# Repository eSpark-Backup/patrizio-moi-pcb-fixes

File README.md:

# PatrizioMoi-PCBFixes

Each product is a audio instrument, where the ESP32 receives audio signals from Ethernet ports (so the Ethernet port and ESP32 must communicate well), and each knob/button/toggle switch sends value signals to the ESP32 for audio processing. The way the audio will be processed it's not an issue right now, because it will be programmed by audio specialist. Your job is to design the 4 PCBS above in a way that

(i) each rotary switch, potentiometers, toggle switch, buttons, etc is aligned wiht the silkscreen and connected to the right pins;  
(ii) each rotary switch, potentiometers, toggle switch, buttons, etc sends signals to the ESP32 correctly;  
(iii) the entire PCB is well powered and fully functioning as desired.

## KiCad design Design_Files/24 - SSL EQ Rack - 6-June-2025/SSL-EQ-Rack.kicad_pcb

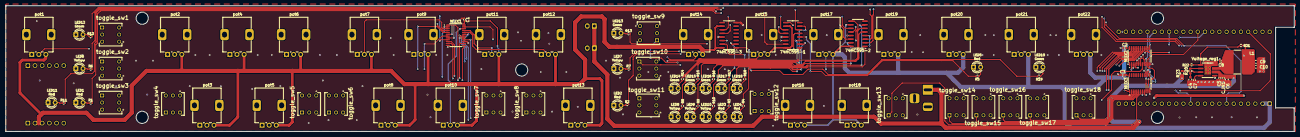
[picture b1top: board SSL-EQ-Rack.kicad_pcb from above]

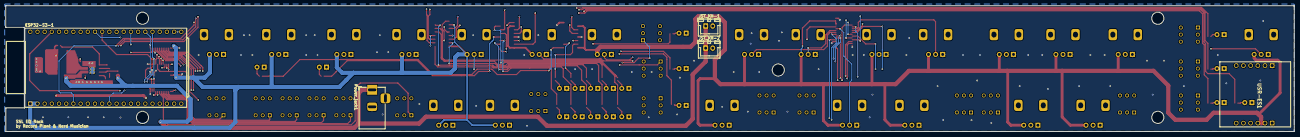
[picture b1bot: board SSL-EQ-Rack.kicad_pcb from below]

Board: 4 copper layers, 455.1 x 44.4 mm, 106 parts (5 on the bottom side), 106 nets.

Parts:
74HC595-1, 74HC595-2, 74HC595-3: 74HC595; SOIC-16_3.9x9.9mm_P1.27mm
C1, C2, C3: 0.1uF; C_0402_1005Metric
C4: 3.3 nF; C_0603_1608Metric
C5, C7, C8: 0.1 µF; C_0402_1005Metric
C6, C9, C10: 22uF; C_0603_1608Metric
C_IN1: 4.7 µF; C_0402_1005Metric
ESP32-S3-1: ESP32-S3-DevKitC; ESP32-S3-DEVKITC-1-N8R2-2
JST_XH-1, JST_XH-2: JST_XH_2_Pin; JST_XH_B2B-XH-A_1x02_P2.50mm_Vertical
L1: 10µH; L_Bourns-SRN8040_8x8.15mm
LED1, LED2, LED3, LED4, LED5, LED11: Red; LED_D3.0mm_Clear-2
LED6, LED7, LED8, LED9, LED10: Yellow; LED_D3.0mm_Clear-2
LED12, LED13, LED14, LED15, LED16, LED17, LED18, LED19: Green; LED_D3.0mm_Clear-2
MUX1, MUX2, MUX3: CD4067BMT/TR; TSSOP-24_4.4x7.8mm_P0.65mm
Power_jack1: Jack-DC; BarrelJack_Horizontal
R1, R2, R3, R4, R5, R6, R7, R8, R9, R10, R11, R12, R13, R14, R15, R16, R17, R18, R19: 330Ω; R_0402_1005Metric
R20: 6.8kΩ; R_0603_1608Metric
R21: 43 kΩ; R_0402_1005Metric
R22: 10 kΩ; R_0402_1005Metric
R23: 100kΩ; R_0603_1608Metric
USR-ES1: USR-ES1; USRES1
Voltage_reg1: MP2307DN-LF-Z; SOIC-8-1EP_3.9x4.9mm_P1.27mm_EP2.29x3mm_ThermalVias
pot1, pot2, pot3, pot4, pot5, pot6, pot7, pot8, pot9, pot10, pot11, pot12, pot13, pot14, pot15, pot16, pot17, pot18, pot19, pot20, pot21, pot22: b10k; Potentiometer_Alps_RK09K_Single_Vertical
toggle_sw1, toggle_sw2, toggle_sw3, toggle_sw4, toggle_sw5, toggle_sw6, toggle_sw7, toggle_sw8, toggle_sw9, toggle_sw10, toggle_sw11, toggle_sw12, toggle_sw13, toggle_sw14, toggle_sw15, toggle_sw16, toggle_sw17, toggle_sw18: button; SW_TL2285EE

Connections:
3.3V: 74HC595-1.10 (~SRCLR), 74HC595-1.16 (VCC), 74HC595-2.10 (~SRCLR), 74HC595-2.16 (VCC), 74HC595-3.10 (~SRCLR), 74HC595-3.16 (VCC), C1.2, C2.2, C3.2, ESP32-S3-1.1 (3V3), ESP32-S3-1.2 (3V3), MUX1.24 (VCC), MUX2.24 (VCC), MUX3.24 (VCC), USR-ES1.B2 (3V3_1), USR-ES1.B3 (3V3_2), pot1.3, pot2.3, pot3.3, pot4.3, pot5.3, pot6.3, pot7.3, pot8.3, pot9.3, pot10.3, pot11.3, pot12.3, pot13.3, pot14.3, pot15.3, pot16.3, pot17.3, pot18.3, pot19.3, pot20.3, pot21.3, pot22.3
/LEDs/LED_A_QA: 74HC595-1.15 (QA), R1.2
/LEDs/LED_A_QB: 74HC595-1.1 (QB), R2.2
/LEDs/LED_A_QC: 74HC595-1.2 (QC), R3.2
/LEDs/LED_A_QD: 74HC595-1.3 (QD), R4.2
/LEDs/LED_A_QE: 74HC595-1.4 (QE), R5.2
/LEDs/LED_A_QF: 74HC595-1.5 (QF), R7.2
/LEDs/LED_A_QG: 74HC595-1.6 (QG), R6.2
/LEDs/LED_A_QH: 74HC595-1.7 (QH), R8.2
/LEDs/LED_B_QA: 74HC595-2.15 (QA), R9.2
/LEDs/LED_B_QB: 74HC595-2.1 (QB), R10.2
/LEDs/LED_B_QC: 74HC595-2.2 (QC), R11.2
/LEDs/LED_B_QD: 74HC595-2.3 (QD), R12.2
/LEDs/LED_B_QE: 74HC595-2.4 (QE), R13.2
/LEDs/LED_B_QF: 74HC595-2.5 (QF), R15.2
/LEDs/LED_B_QG: 74HC595-2.6 (QG), R14.2
/LEDs/LED_B_QH: 74HC595-2.7 (QH), R16.2
/LEDs/LED_C_QA: 74HC595-3.15 (QA), R18.2
/LEDs/LED_C_QB: 74HC595-3.1 (QB), R19.2
/LEDs/LED_C_QC: 74HC595-3.2 (QC), R17.2
BOOT: C8.2, Voltage_reg1.1 (BS)
CS: ESP32-S3-1.5 (GPIO5/ADC1_CH4), USR-ES1.A5 (CS)
EXT_12V: C5.1, C6.2, C_IN1.1, JST_XH-1.1, JST_XH-2.1, Power_jack1.1, R23.1, Voltage_reg1.2 (IN)
GND: 74HC595-1.8 (GND), 74HC595-1.13 (~OE), 74HC595-2.8 (GND), 74HC595-2.13 (~OE), 74HC595-3.8 (GND), 74HC595-3.13 (~OE), C1.1, C2.1, C3.1, C4.2, C5.2, C6.1, C7.2, C9.2, C10.2, C_IN1.2, ESP32-S3-1.22 (GND), ESP32-S3-1.23 (GND), ESP32-S3-1.24 (GND), ESP32-S3-1.44 (GND), JST_XH-1.2, JST_XH-2.2, LED1.1 (K), LED2.1 (K), LED3.1 (K), LED4.1 (K), LED5.1 (K), LED6.1 (K), LED7.1 (K), LED8.1 (K), LED9.1 (K), LED10.1 (K), LED11.1 (K), LED12.1 (K), LED13.1 (K), LED14.1 (K), LED15.1 (K), LED16.1 (K), LED17.1 (K), LED18.1 (K), LED19.1 (K), MUX1.12 (GND), MUX1.15 (~E), MUX2.12 (GND), MUX2.15 (~E), MUX3.12 (GND), MUX3.15 (~E), Power_jack1.2, R22.2, USR-ES1.A1 (GND_1), USR-ES1.A2 (GND_2), USR-ES1.B1 (GND_3), Voltage_reg1.4 (GND), Voltage_reg1.9 (EP), pot1.1, pot2.1, pot3.1, pot4.1, pot5.1, pot6.1, pot7.1, pot8.1, pot9.1, pot10.1, pot11.1, pot12.1, pot13.1, pot14.1, pot15.1, pot16.1, pot17.1, pot18.1, pot19.1, pot20.1, pot21.1, pot22.1, toggle_sw1.3, toggle_sw2.3, toggle_sw3.3, toggle_sw4.3, toggle_sw5.3, toggle_sw6.3, toggle_sw7.3, toggle_sw8.3, toggle_sw9.3, toggle_sw10.3, toggle_sw11.3, toggle_sw12.3, toggle_sw13.3, toggle_sw14.3, toggle_sw15.3, toggle_sw16.3, toggle_sw17.3, toggle_sw18.3
I0: MUX1.9 (I0), pot1.2
I1: MUX1.8 (I1), pot2.2
I2: MUX1.7 (I2), pot3.2
I3: MUX1.6 (I3), pot4.2
I4: MUX1.5 (I4), pot5.2
I5: MUX1.4 (I5), pot6.2
I6: MUX1.3 (I6), pot7.2
I7: MUX1.2 (I7), pot8.2
I8: MUX1.23 (I8), pot9.2
I9: MUX1.22 (I9), pot10.2
I10: MUX1.21 (I10), pot11.2
I11: MUX1.20 (I11), pot12.2
I12: MUX1.19 (I12), pot13.2
I13: MUX1.18 (I13), pot14.2
I14: MUX1.17 (I14), pot15.2
I15: MUX1.16 (I15), pot16.2
INT: ESP32-S3-1.7 (GPIO7/ADC1_CH6), USR-ES1.A6 (INT)
J0: MUX2.9 (I0), pot17.2
J1: MUX2.8 (I1), pot18.2
J2: MUX2.7 (I2), pot19.2
J3: MUX2.6 (I3), pot20.2
J4: MUX2.5 (I4), pot21.2
J5: MUX2.4 (I5), pot22.2
J6: MUX2.3 (I6), toggle_sw1.1
J7: MUX2.2 (I7), toggle_sw2.1
J8: MUX2.23 (I8), toggle_sw3.1
J9: MUX2.22 (I9), toggle_sw4.1
J10: MUX2.21 (I10), toggle_sw5.1
J11: MUX2.20 (I11), toggle_sw6.1
J12: MUX2.19 (I12), toggle_sw7.1
J13: MUX2.18 (I13), toggle_sw8.1
J14: MUX2.17 (I14), toggle_sw9.1
J15: MUX2.16 (I15), toggle_sw10.1
K0: MUX3.9 (I0), toggle_sw11.1
K1: MUX3.8 (I1), toggle_sw12.1
K2: MUX3.7 (I2), toggle_sw13.1
K3: MUX3.6 (I3), toggle_sw14.1
K4: MUX3.5 (I4), toggle_sw15.1
K5: MUX3.4 (I5), toggle_sw16.1
K6: MUX3.3 (I6), toggle_sw17.1
K7: MUX3.2 (I7), toggle_sw18.1
MISO: ESP32-S3-1.33 (GPIO36), USR-ES1.B6 (MISO)
MOSI: ESP32-S3-1.32 (GPIO35), USR-ES1.A3 (MOSI)
unnamed: 74HC595-1.9 (QH'), 74HC595-2.14 (SER)
unnamed: 74HC595-2.9 (QH'), 74HC595-3.14 (SER)
unnamed: C4.1, R20.1
unnamed: LED1.2 (A), R1.1
unnamed: LED2.2 (A), R2.1
unnamed: LED3.2 (A), R3.1
unnamed: LED4.2 (A), R4.1
unnamed: LED5.2 (A), R5.1
unnamed: LED6.2 (A), R6.1
unnamed: LED7.2 (A), R7.1
unnamed: LED8.2 (A), R8.1
unnamed: LED9.2 (A), R9.1
unnamed: LED10.2 (A), R10.1
unnamed: LED11.2 (A), R11.1
unnamed: LED12.2 (A), R12.1
unnamed: LED13.2 (A), R13.1
unnamed: LED14.2 (A), R14.1
unnamed: LED15.2 (A), R15.1
unnamed: LED16.2 (A), R16.1
unnamed: LED17.2 (A), R17.1
unnamed: LED18.2 (A), R18.1
unnamed: LED19.2 (A), R19.1
unnamed: R20.2, Voltage_reg1.6 (COMP)
unnamed: R23.2, Voltage_reg1.7 (EN)
unnamed: R21.2, R22.1, Voltage_reg1.5 (FB)
unnamed: C7.1, Voltage_reg1.8 (SS)
unnamed: C8.1, L1.1, Voltage_reg1.3 (SW)
RCLK_latch: 74HC595-1.12 (RCLK), 74HC595-2.12 (RCLK), 74HC595-3.12 (RCLK), ESP32-S3-1.40 (GPIO2/ADC1_CH1)
REG_5V: C9.1, C10.1, ESP32-S3-1.21 (5V), L1.2, R21.1
RST: ESP32-S3-1.35 (GPIO38), USR-ES1.B5 (RST)
S0: ESP32-S3-1.27 (GPIO21), MUX1.10 (S0), MUX2.10 (S0), MUX3.10 (S0)
S1: ESP32-S3-1.34 (GPIO37), MUX1.11 (S1), MUX2.11 (S1), MUX3.11 (S1)
S2: ESP32-S3-1.30 (GPIO45), MUX1.14 (S2), MUX2.14 (S2), MUX3.14 (S2)
S3: ESP32-S3-1.28 (GPIO47), MUX1.13 (S3), MUX2.13 (S3), MUX3.13 (S3)
SCLK: 74HC595-1.11 (SRCLK), 74HC595-2.11 (SRCLK), 74HC595-3.11 (SRCLK), ESP32-S3-1.11 (GPIO18/ADC2_CH7), USR-ES1.A4 (SCLK)
SER: 74HC595-1.14 (SER), ESP32-S3-1.4 (GPIO4/ADC1_CH3)
sig_1: ESP32-S3-1.41 (GPIO1/ADC1_CH0), MUX1.1 (COM)
sig_2: ESP32-S3-1.13 (GPIO3/ADC1_CH2), MUX2.1 (COM)
sig_3: ESP32-S3-1.12 (GPIO8/ADC1_CH7), MUX3.1 (COM)

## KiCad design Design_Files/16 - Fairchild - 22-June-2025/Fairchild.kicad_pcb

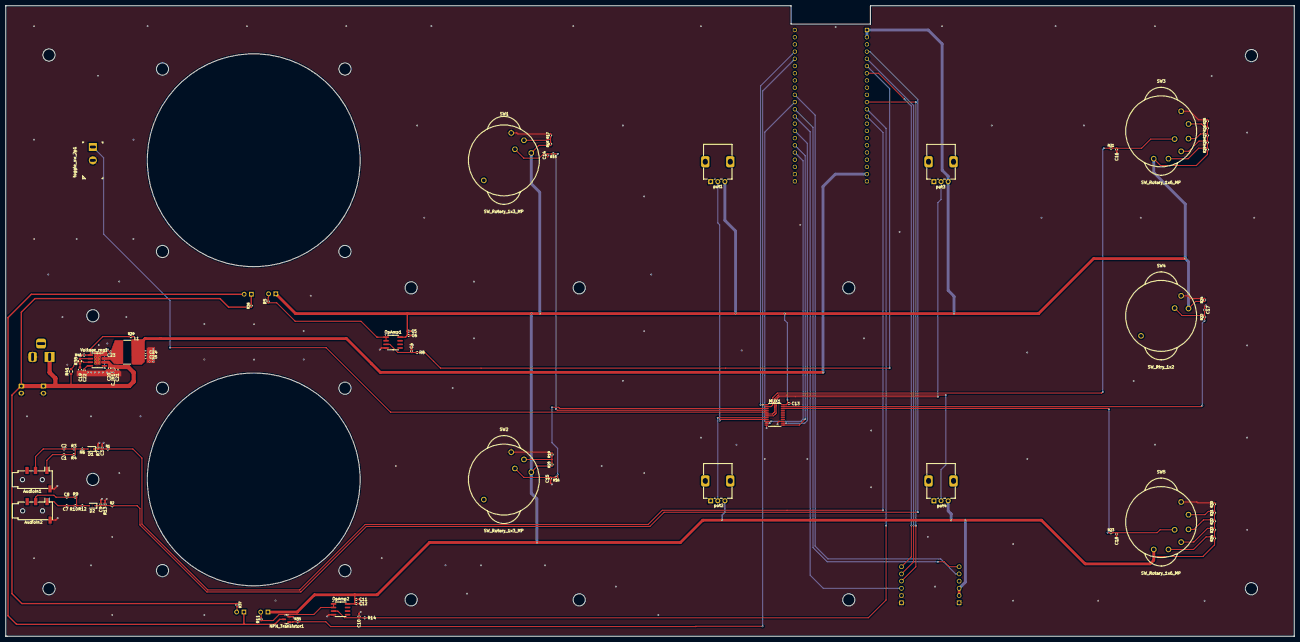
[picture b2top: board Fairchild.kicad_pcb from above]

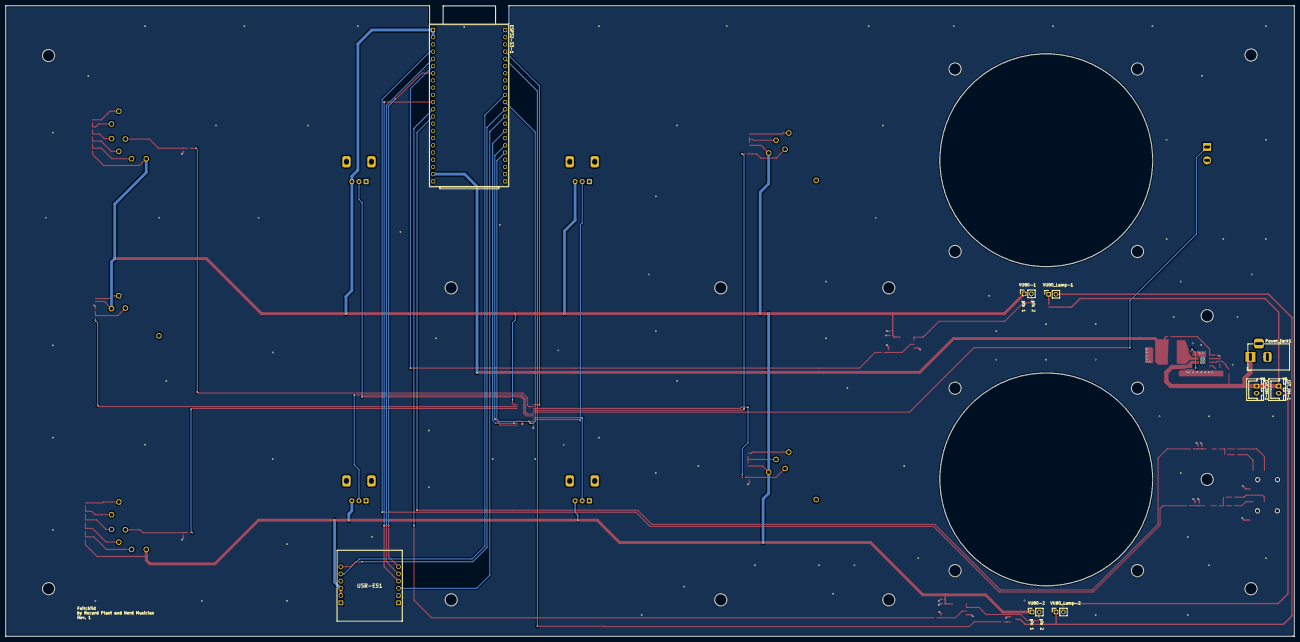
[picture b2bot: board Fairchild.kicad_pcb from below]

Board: 2 copper layers, 454.1 x 222.2 mm, 96 parts (9 on the bottom side), 76 nets.

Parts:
AudioIn1, AudioIn2: AudioIn; Jack_3.5mm_PJ320D_Horizontal
C1, C2, C3, C5, C7, C8, C9, C11: 4.7uF; C_0402_1005Metric
C4, C6, C10, C12, C13: 0.1uF; C_0402_1005Metric
C14, C15, C16, C17, C18: 2.2uF; C_0402_1005Metric
C19: 3.3 nF; C_0603_1608Metric
C20, C22, C23: 0.1 µF; C_0402_1005Metric
C21, C24, C25: 22uF; C_0603_1608Metric
C_IN1: 4.7 µF; C_0402_1005Metric
D1, D2: BAT54SW; D_SOD-323
ESP32-S3-1: ESP32-S3-DevKitC; ESP32-S3-DEVKITC-1-N8R2-2
JST_XH-1, JST_XH-2: JST_XH_2_Pin; JST_XH_B2B-XH-A_1x02_P2.50mm_Vertical
L1: 10µH; L_Bourns-SRN8040_8x8.15mm
MUX1: CD4067BMT/TR; TSSOP-24_4.4x7.8mm_P0.65mm
NPN_Transistor1: 2N2219; SOT-23
OpAmp1, OpAmp2: MCP6002; SOIC-8_3.9x4.9mm_P1.27mm
Power_jack1: Jack-DC; BarrelJack_Horizontal
R1, R2: 4.7KΩ; R_0402_1005Metric
R3, R4, R5, R6, R9, R10, R11, R12: 10KΩ; C_0402_1005Metric
R7, R13: 47KΩ; C_0402_1005Metric
R8, R14: 92R; C_0402_1005Metric
R15, R16, R21, R22, R23: 100Ω; R_0402_1005Metric
R17, R18, R19, R20, R24, R25, R26, R27, R28, R29, R30, R31, R32, R33, R34: 2.2KΩ; R_0402_1005Metric
R35: 1kΩ; R_0402_1005Metric
R36, R37: 80Ω; R_0402_1005Metric
R38: 6.8kΩ; R_0603_1608Metric
R39: 43 kΩ; R_0402_1005Metric
R40: 10 kΩ; R_0402_1005Metric
R41: 100kΩ; R_0603_1608Metric
SW1, SW2: SW_Rotary_1x3_MP; SW_Rotary_RS25-3P
SW3, SW5: SW_Rotary_1x6_MP; SW_Rotary_RS25-6P
SW4: SW_Rtry_1x2; SW_Rotary_RS25-2P
USR-ES1: USR-ES1; USRES1
VU80-1, VU80-2: VU80; PinSocket_1x02_P2.54mm_Vertical
VU80_Lamp-1, VU80_Lamp-2: VU80_Lamp; PinSocket_1x02_P2.54mm_Vertical
Voltage_reg1: MP2307DN-LF-Z; SOIC-8-1EP_3.9x4.9mm_P1.27mm_EP2.29x3mm_ThermalVias
pot1, pot2, pot3, pot4: b10k; Potentiometer_Alps_RK09K_Single_Vertical
toggle_sw_2p1: SW_SPST; Toggle_Switch-2-pins

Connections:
3.3V: C5.2, C6.2, C11.2, C12.2, C13.2, ESP32-S3-1.1 (3V3), ESP32-S3-1.2 (3V3), MUX1.24 (VCC), OpAmp1.8 (VCC), OpAmp2.8 (VCC), R18.1, R20.1, R24.1, R29.1, R34.1, SW1.3, SW2.3, SW3.6, SW4.2, SW5.6, USR-ES1.B2 (3V3_1), USR-ES1.B3 (3V3_2), VU80-1.1, VU80-2.1, pot1.3, pot2.3, pot3.3, pot4.3
AUDIO_IN_1: C3.1, D1.1 (K), R1.1, R7.2
AUDIO_IN_2: C9.1, D2.1 (K), R2.1, R13.2
BOOT: C23.2, Voltage_reg1.1 (BS)
CS: ESP32-S3-1.5 (GPIO5/ADC1_CH4), USR-ES1.A5 (CS)
EXT_12V: C20.1, C21.2, C_IN1.1, JST_XH-1.1, JST_XH-2.1, Power_jack1.1, R36.1, R37.1, R41.1, Voltage_reg1.2 (IN)
GND: AudioIn1.S, AudioIn2.S, C3.2, C4.1, C5.1, C6.1, C9.2, C10.1, C11.1, C12.1, C13.1, C14.1, C15.1, C16.1, C17.1, C18.1, C19.2, C20.2, C21.1, C22.2, C24.2, C25.2, C_IN1.2, ESP32-S3-1.22 (GND), ESP32-S3-1.23 (GND), ESP32-S3-1.24 (GND), ESP32-S3-1.44 (GND), JST_XH-1.2, JST_XH-2.2, MUX1.12 (GND), MUX1.15 (~E), NPN_Transistor1.2 (E), OpAmp1.4 (GND), OpAmp2.4 (GND), Power_jack1.2, R7.1, R13.1, R17.2, R19.2, R24.2, R25.2, R30.2, R40.2, SW1.1, SW2.1, SW3.1, SW4.1, SW5.1, USR-ES1.A1 (GND_1), USR-ES1.A2 (GND_2), USR-ES1.B1 (GND_3), Voltage_reg1.4 (GND), Voltage_reg1.9 (EP), pot1.1, pot2.1, pot3.1, pot4.1, toggle_sw_2p1.2 (B)
I0: MUX1.9 (I0), pot1.2
I1: MUX1.8 (I1), pot2.2
I2: MUX1.7 (I2), pot3.2
I3: MUX1.6 (I3), pot4.2
I4: MUX1.5 (I4), toggle_sw_2p1.1 (A)
I5: MUX1.4 (I5), R15.1
I6: MUX1.3 (I6), R16.1
I7: MUX1.2 (I7), R21.1
I8: MUX1.23 (I8), R22.1
I9: MUX1.22 (I9), R23.1
INT: ESP32-S3-1.7 (GPIO7/ADC1_CH6), USR-ES1.A6 (INT)
MISO: ESP32-S3-1.33 (GPIO36), USR-ES1.B6 (MISO)
MOSI: ESP32-S3-1.32 (GPIO35), USR-ES1.A3 (MOSI)
unnamed: AudioIn1.R, C2.2
unnamed: AudioIn1.T, C1.1
unnamed: AudioIn2.R, C8.2
unnamed: AudioIn2.T, C7.1
unnamed: C1.2, R4.2
unnamed: C2.1, R3.2
unnamed: C7.2, R10.2
unnamed: C8.1, R9.2
unnamed: C14.2, R15.2, SW1.C
unnamed: C15.2, R16.2, SW2.C
unnamed: C16.2, R21.2, SW3.C
unnamed: C17.2, R22.2, SW4.C
unnamed: C18.2, R23.2, SW5.C
unnamed: C19.1, R38.1
unnamed: D1.2 (A), R6.1
unnamed: D2.2 (A), R12.1
unnamed: ESP32-S3-1.13 (GPIO3/ADC1_CH2), R1.2
unnamed: ESP32-S3-1.4 (GPIO4/ADC1_CH3), R2.2
unnamed: NPN_Transistor1.1 (B), R35.1
unnamed: NPN_Transistor1.3 (C), VU80_Lamp-1.2, VU80_Lamp-2.1
unnamed: C4.2, OpAmp1.3 (+), R8.1
unnamed: C10.2, OpAmp2.3 (+), R14.1
unnamed: R3.1, R4.1, R6.2
unnamed: R9.1, R10.1, R12.2
unnamed: R17.1, R18.2, SW1.2
unnamed: R19.1, R20.2, SW2.2
unnamed: R25.1, R26.2, SW3.2
unnamed: R26.1, R27.2, SW3.3
unnamed: R27.1, R28.2, SW3.4
unnamed: R28.1, R29.2, SW3.5
unnamed: R30.1, R31.2, SW5.2
unnamed: R31.1, R32.2, SW5.3
unnamed: R32.1, R33.2, SW5.4
unnamed: R33.1, R34.2, SW5.5
unnamed: R5.2, VU80-1.2
unnamed: R11.2, VU80-2.2
unnamed: R36.2, VU80_Lamp-1.1
unnamed: R37.2, VU80_Lamp-2.2
unnamed: R38.2, Voltage_reg1.6 (COMP)
unnamed: R41.2, Voltage_reg1.7 (EN)
unnamed: R39.2, R40.1, Voltage_reg1.5 (FB)
unnamed: C22.1, Voltage_reg1.8 (SS)
unnamed: C23.1, L1.1, Voltage_reg1.3 (SW)
REG_5V: C24.1, C25.1, ESP32-S3-1.21 (5V), L1.2, R39.1
RST: ESP32-S3-1.35 (GPIO38), USR-ES1.B5 (RST)
S0: ESP32-S3-1.27 (GPIO21), MUX1.10 (S0)
S1: ESP32-S3-1.34 (GPIO37), MUX1.11 (S1)
S2: ESP32-S3-1.30 (GPIO45), MUX1.14 (S2)
S3: ESP32-S3-1.28 (GPIO47), MUX1.13 (S3)
SCLK: ESP32-S3-1.11 (GPIO18/ADC2_CH7), USR-ES1.A4 (SCLK)
VU_DRIVE: OpAmp1.1, OpAmp1.2 (-), R5.1
VU_DRIVE_2: OpAmp2.1, OpAmp2.2 (-), R11.1
VU_uC_1: ESP32-S3-1.6 (GPIO6/ADC1_CH5), R8.2
VU_uC_2: ESP32-S3-1.12 (GPIO8/ADC1_CH7), R14.2
led_VU: ESP32-S3-1.40 (GPIO2/ADC1_CH1), R35.2
sig_1: ESP32-S3-1.41 (GPIO1/ADC1_CH0), MUX1.1 (COM)

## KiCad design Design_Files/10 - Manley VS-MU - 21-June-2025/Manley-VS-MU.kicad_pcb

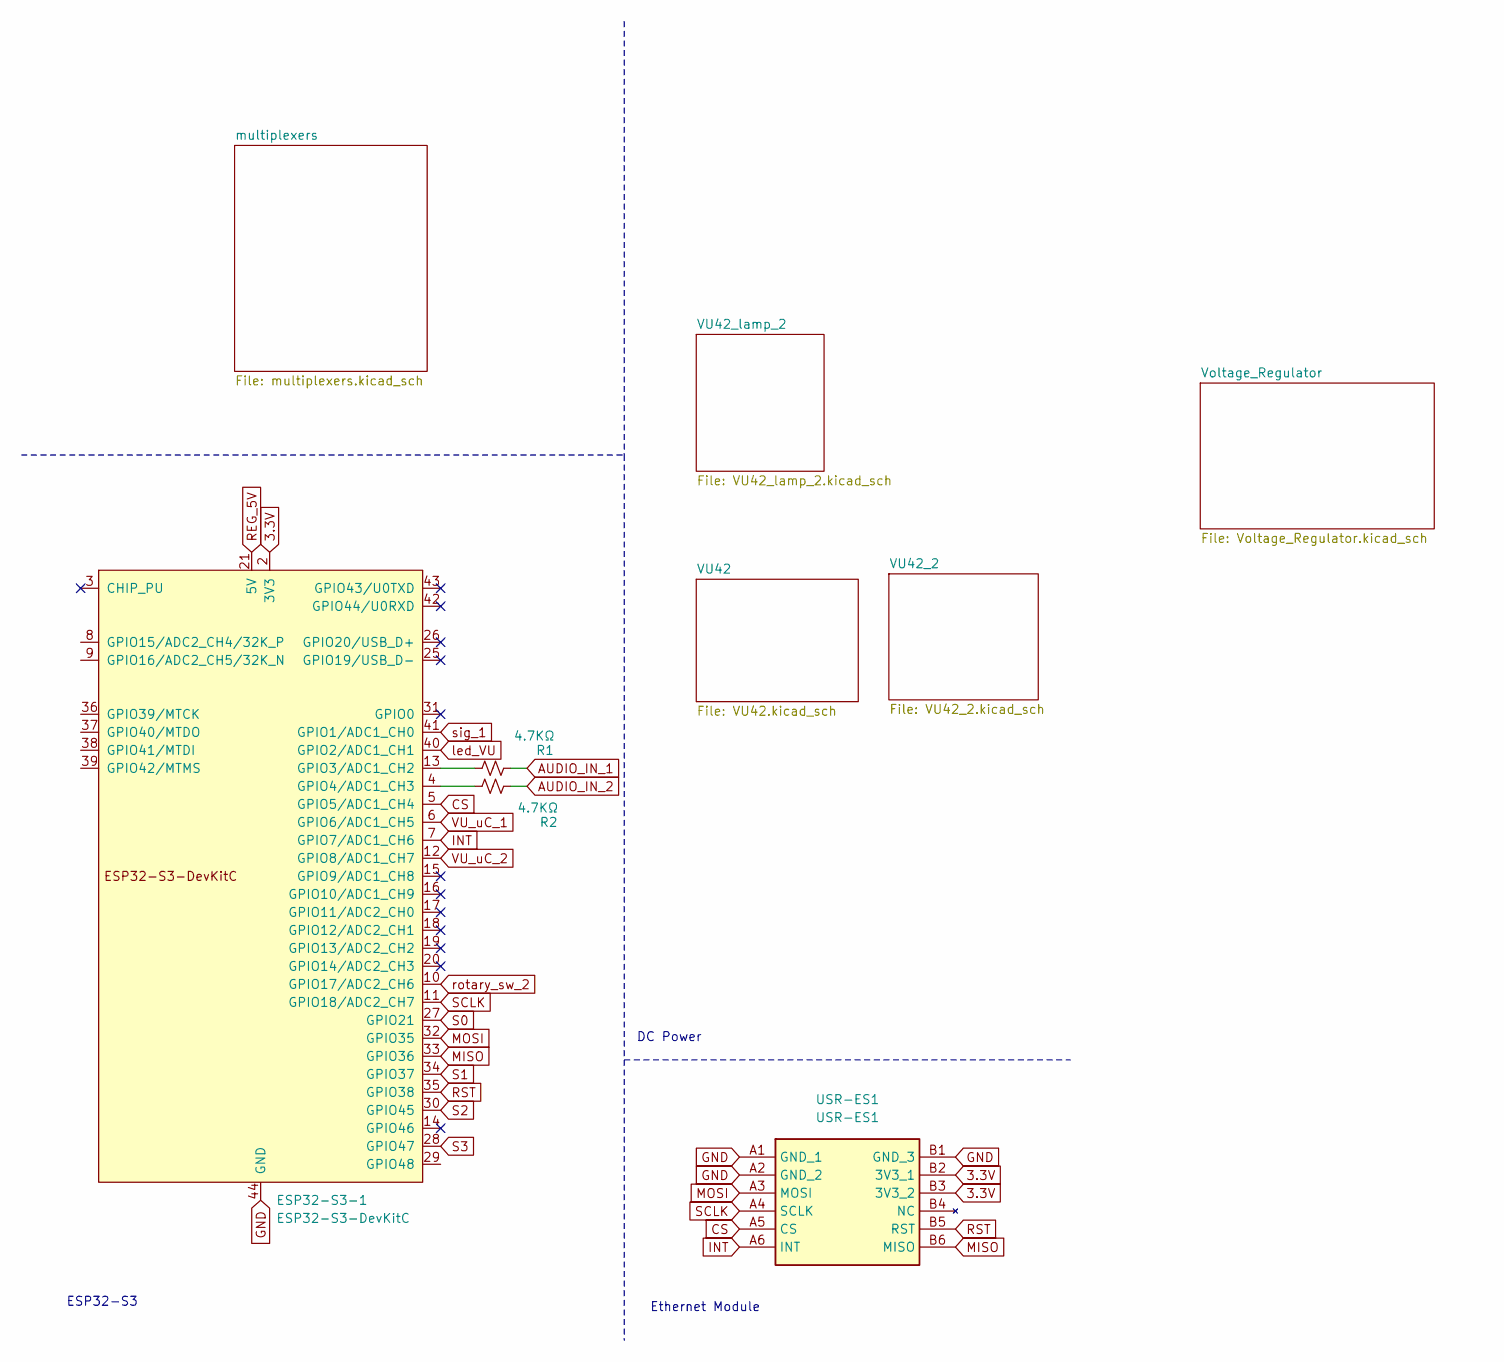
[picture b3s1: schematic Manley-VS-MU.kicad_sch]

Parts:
ESP32-S3-1: ESP32-S3-DevKitC; ESP32-S3-DEVKITC-1-N8R2-2; PARTREV V1
R1, R2: 4.7KΩ; R_0402_1005Metric; LCSC Part Number C25900
USR-ES1: USR-ES1; USRES1; Manufacturer_Part_Number USR-ES1

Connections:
3.3V: ESP32-S3-1.1 (3V3), ESP32-S3-1.2 (3V3), USR-ES1.B2 (3V3_1), USR-ES1.B3 (3V3_2); also elsewhere on the board
AUDIO_IN_1: R1.1; also elsewhere on the board
AUDIO_IN_2: R2.1; also elsewhere on the board
CS: ESP32-S3-1.5 (GPIO5/ADC1_CH4), USR-ES1.A5 (CS)
GND: ESP32-S3-1.22 (GND), ESP32-S3-1.23 (GND), ESP32-S3-1.24 (GND), ESP32-S3-1.44 (GND), USR-ES1.A1 (GND_1), USR-ES1.A2 (GND_2), USR-ES1.B1 (GND_3); also elsewhere on the board
INT: ESP32-S3-1.7 (GPIO7/ADC1_CH6), USR-ES1.A6 (INT)
MISO: ESP32-S3-1.33 (GPIO36), USR-ES1.B6 (MISO)
MOSI: ESP32-S3-1.32 (GPIO35), USR-ES1.A3 (MOSI)
unnamed: ESP32-S3-1.13 (GPIO3/ADC1_CH2), R1.2
unnamed: ESP32-S3-1.4 (GPIO4/ADC1_CH3), R2.2
REG_5V: ESP32-S3-1.21 (5V); also elsewhere on the board
RST: ESP32-S3-1.35 (GPIO38), USR-ES1.B5 (RST)
S0: ESP32-S3-1.27 (GPIO21); also elsewhere on the board
S1: ESP32-S3-1.34 (GPIO37); also elsewhere on the board
S2: ESP32-S3-1.30 (GPIO45); also elsewhere on the board
S3: ESP32-S3-1.28 (GPIO47); also elsewhere on the board
SCLK: ESP32-S3-1.11 (GPIO18/ADC2_CH7), USR-ES1.A4 (SCLK)
VU_uC_1: ESP32-S3-1.6 (GPIO6/ADC1_CH5); also elsewhere on the board
VU_uC_2: ESP32-S3-1.12 (GPIO8/ADC1_CH7); also elsewhere on the board
led_VU: ESP32-S3-1.40 (GPIO2/ADC1_CH1); also elsewhere on the board
rotary_sw_2: ESP32-S3-1.10 (GPIO17/ADC2_CH6); also elsewhere on the board
sig_1: ESP32-S3-1.41 (GPIO1/ADC1_CH0); also elsewhere on the board

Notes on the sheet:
Ethernet Module
DC Power
ESP32-S3

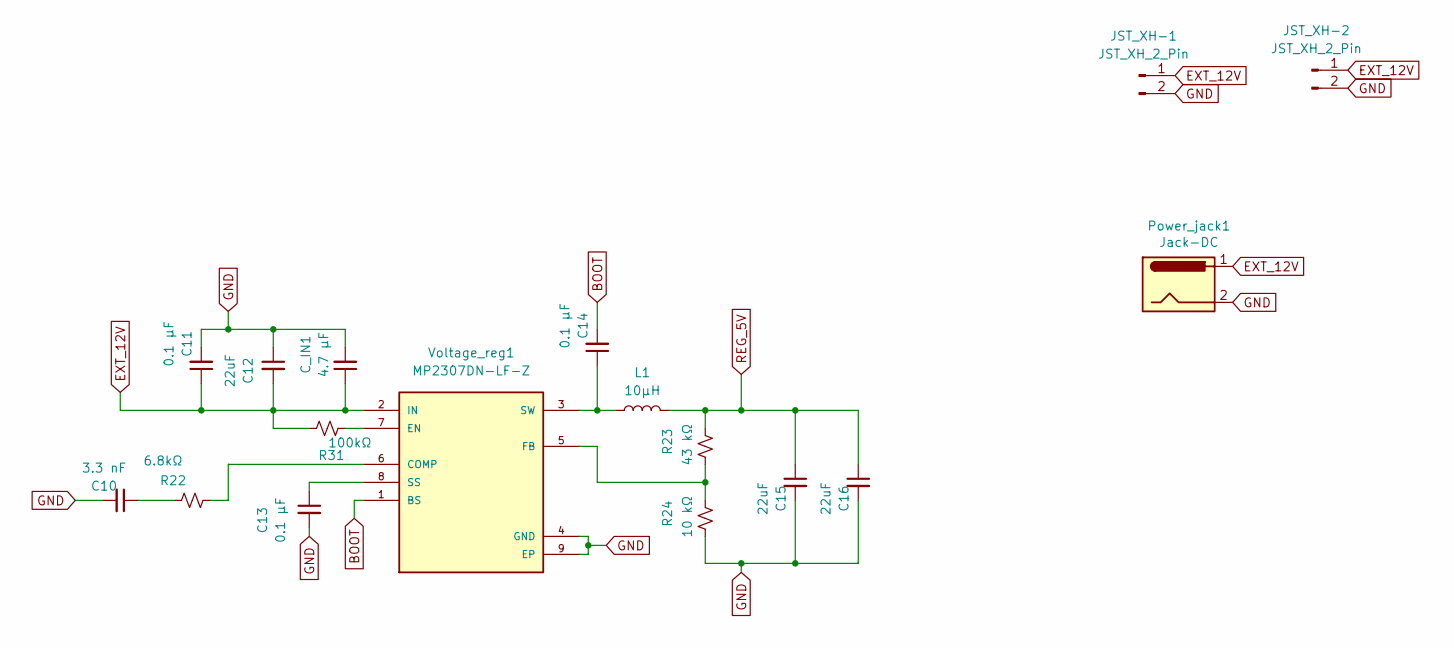
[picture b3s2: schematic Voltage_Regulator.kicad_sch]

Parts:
C10: 3.3 nF; C_0603_1608Metric; LCSC Part Number C1613
C11, C13, C14: 0.1 µF; C_0402_1005Metric; LCSC Part Number C1525
C12, C15, C16: 22uF; C_0603_1608Metric; LCSC Part Number C59461
C_IN1: 4.7 µF; C_0402_1005Metric; LCSC Part Number C23733
JST_XH-1, JST_XH-2: JST_XH_2_Pin; JST_XH_B2B-XH-A_1x02_P2.50mm_Vertical
L1: 10µH; L_Bourns-SRN8040_8x8.15mm; LCSC Part Number C37429
Power_jack1: Jack-DC; BarrelJack_Horizontal
R22: 6.8kΩ; R_0603_1608Metric; LCSC Part Number C23212
R23: 43 kΩ; R_0402_1005Metric; LCSC Part Number C2906943
R24: 10 kΩ; R_0402_1005Metric; LCSC Part Number C25744
R31: 100kΩ; R_0603_1608Metric
Voltage_reg1: MP2307DN-LF-Z; SOIC-8-1EP_3.9x4.9mm_P1.27mm_EP2.29x3mm_ThermalVias; PARTREV 1.9; LCSC Part Number C2928813

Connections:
BOOT: C14.2, Voltage_reg1.1 (BS)
EXT_12V: C11.1, C12.2, C_IN1.1, JST_XH-1.1, JST_XH-2.1, Power_jack1.1, R31.1, Voltage_reg1.2 (IN); also elsewhere on the board
GND: C10.2, C11.2, C12.1, C13.2, C15.2, C16.2, C_IN1.2, JST_XH-1.2, JST_XH-2.2, Power_jack1.2, R24.2, Voltage_reg1.4 (GND), Voltage_reg1.9 (EP); also elsewhere on the board
unnamed: C10.1, R22.1
unnamed: R22.2, Voltage_reg1.6 (COMP)
unnamed: R31.2, Voltage_reg1.7 (EN)
unnamed: R23.2, R24.1, Voltage_reg1.5 (FB)
unnamed: C13.1, Voltage_reg1.8 (SS)
unnamed: C14.1, L1.1, Voltage_reg1.3 (SW)
REG_5V: C15.1, C16.1, L1.2, R23.1; also elsewhere on the board

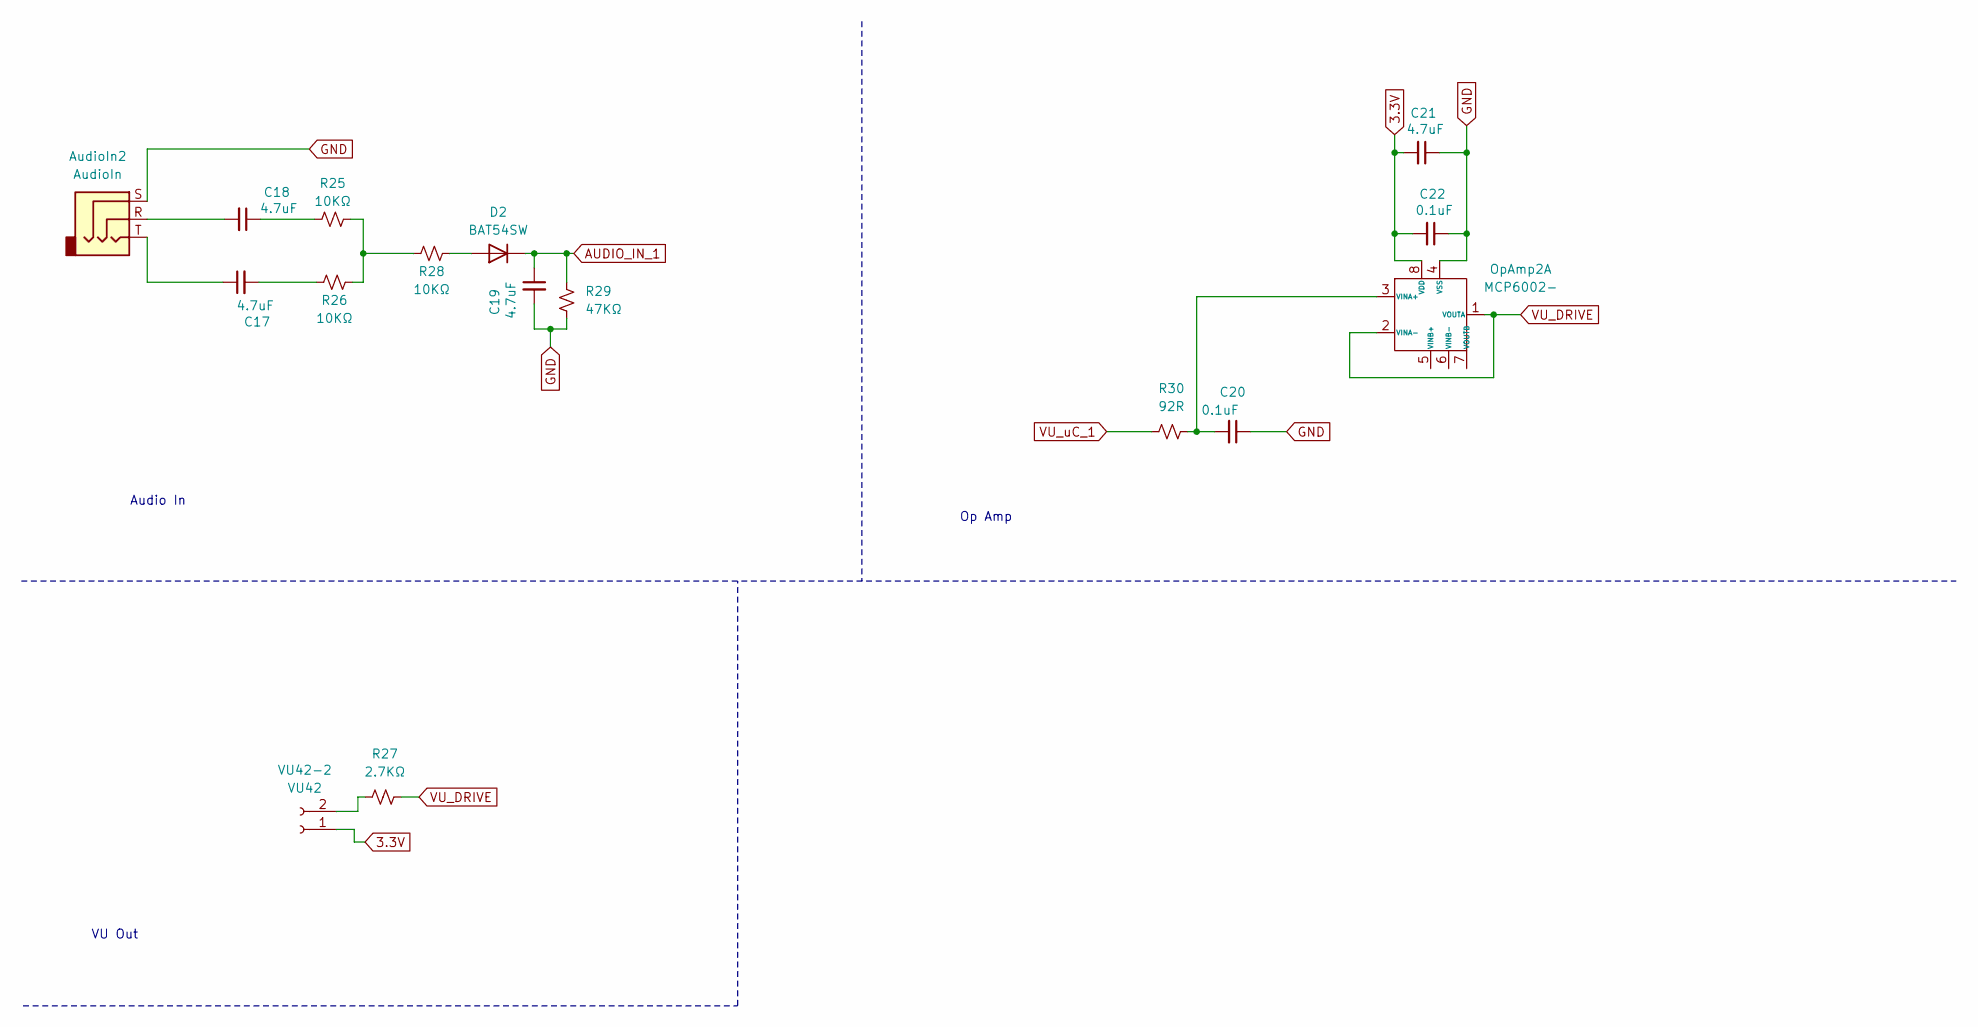
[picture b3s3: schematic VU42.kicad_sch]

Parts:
AudioIn2: AudioIn; Jack_3.5mm_PJ320D_Horizontal; LCSC Part Number C22459515
C17, C18, C19, C21: 4.7uF; C_0402_1005Metric; LCSC Part Number C23733
C20: 0.1uF; C_0402_1005Metric
C22: 0.1uF; C_0402_1005Metric; LCSC Part Number C1525
D2: BAT54SW; D_SOD-323; LCSC Part Number C27636114
OpAmp2: MCP6002-; SOIC-8_3.9x4.9mm_P1.27mm; LCSC Part Number C7377
R25, R26, R28: 10KΩ; R_0402_1005Metric; LCSC Part Number C25744
R27: 2.7KΩ; R_0603_1608Metric; LCSC Part Number C13167
R29: 47KΩ; R_0402_1005Metric; LCSC Part Number C25792
R30: 92R; R_0402_1005Metric
VU42-2: VU42; PinSocket_1x02_P2.54mm_Vertical

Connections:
3.3V: C21.2, C22.2, OpAmp2.8 (VDD), VU42-2.1; also elsewhere on the board
AUDIO_IN_1: C19.1, D2.1 (K), R29.2; also elsewhere on the board
GND: AudioIn2.S, C19.2, C20.1, C21.1, C22.1, OpAmp2.4 (VSS), R29.1; also elsewhere on the board
unnamed: AudioIn2.R, C18.2
unnamed: AudioIn2.T, C17.1
unnamed: C17.2, R26.2
unnamed: C18.1, R25.2
unnamed: D2.2 (A), R28.1
unnamed: C20.2, OpAmp2.3 (VINA+), R30.1
unnamed: R25.1, R26.1, R28.2
unnamed: R27.2, VU42-2.2
VU_DRIVE: OpAmp2.1 (VOUTA), OpAmp2.2 (VINA-), R27.1
VU_uC_1: R30.2; also elsewhere on the board

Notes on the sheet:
VU Out
Op Amp
Audio In

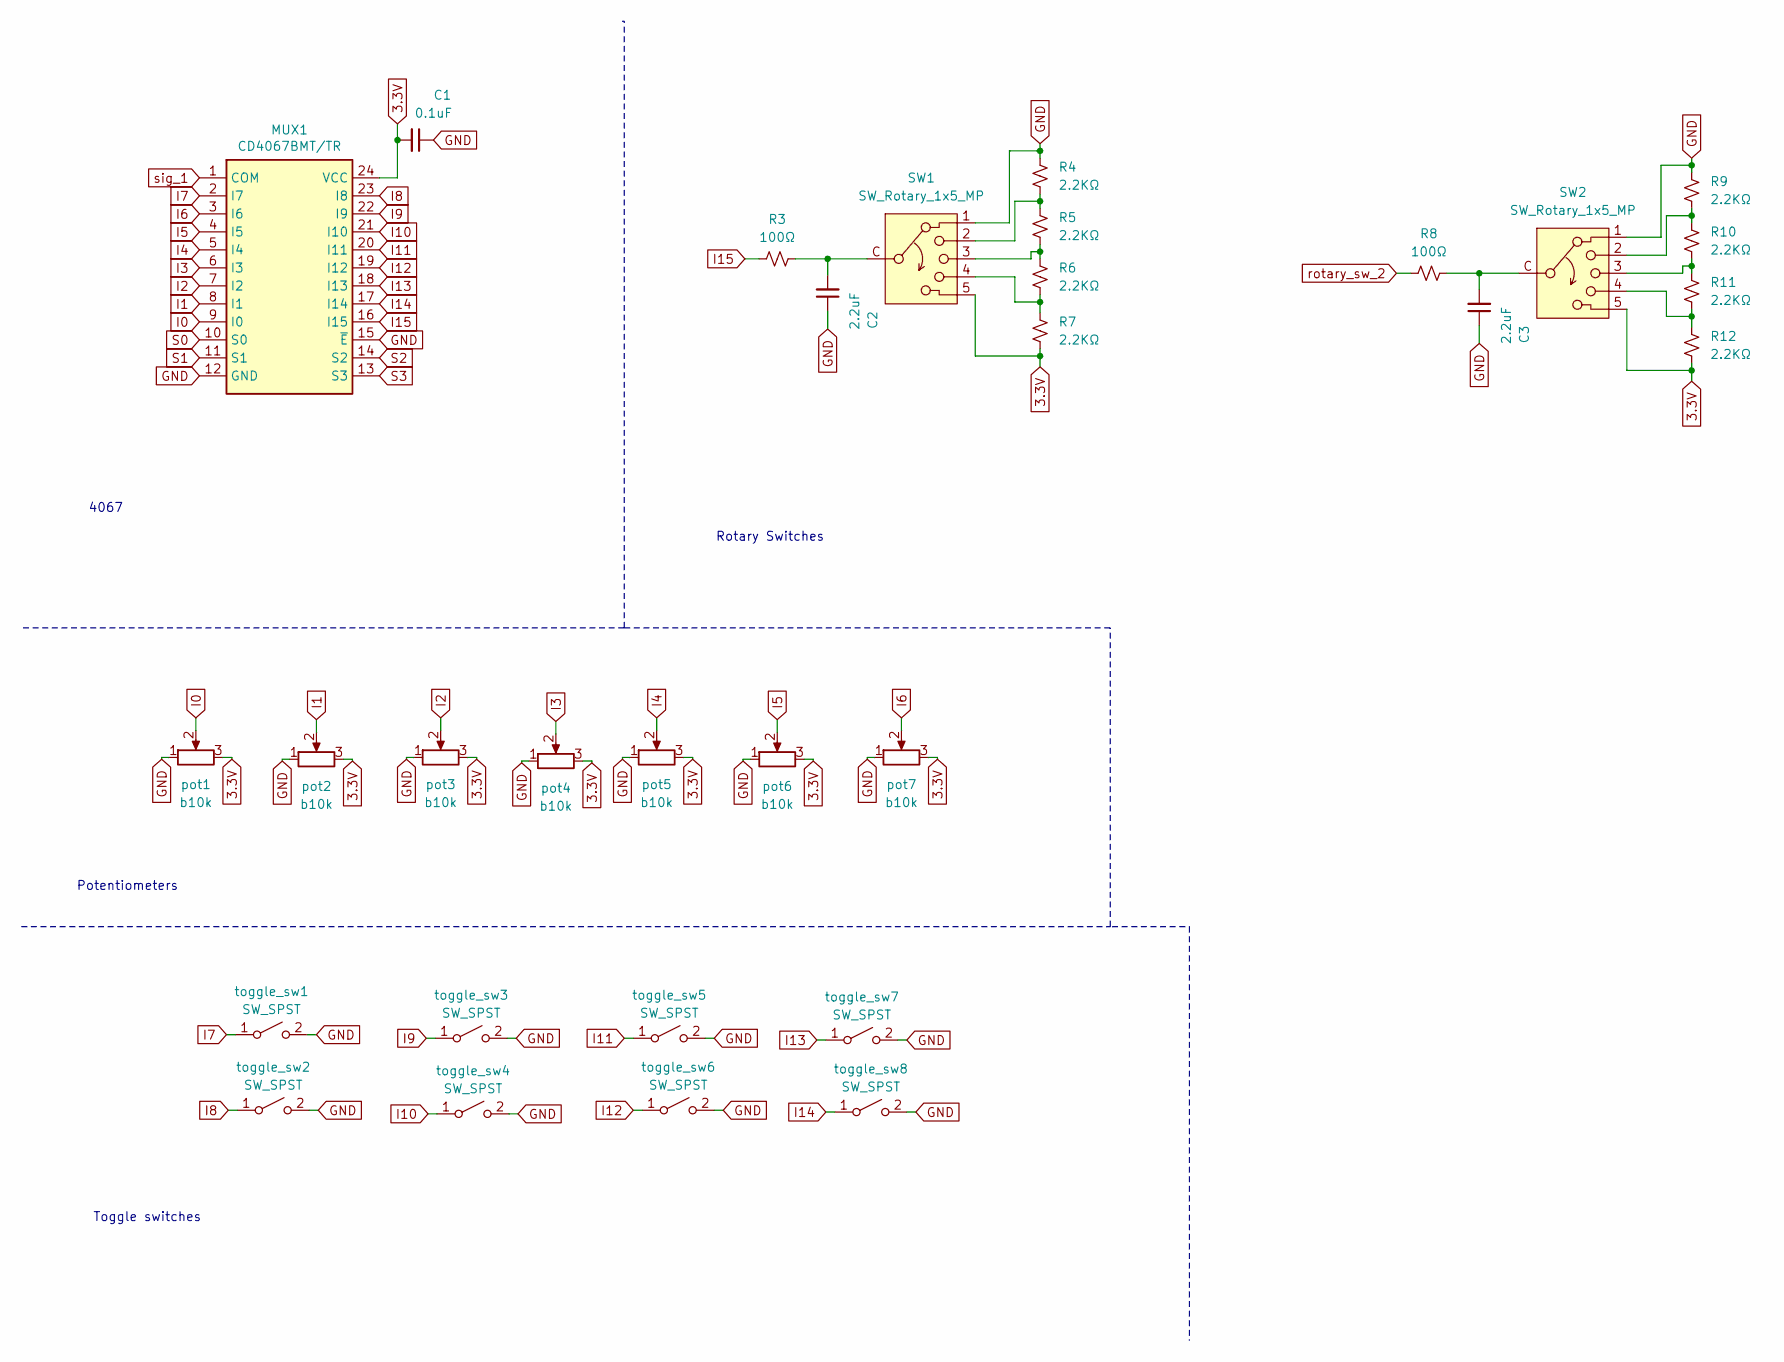
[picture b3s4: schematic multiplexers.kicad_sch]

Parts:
C1: 0.1uF; C_0402_1005Metric; LCSC Part Number C14663
C2, C3: 2.2uF; C_0402_1005Metric; LCSC Part Number C12530
MUX1: CD4067BMT/TR; TSSOP-24_4.4x7.8mm_P0.65mm; LCSC Part Number C7432333
R3, R8: 100Ω; R_0402_1005Metric; LCSC Part Number C25076
R4, R5, R6, R7, R9, R10, R11, R12: 2.2KΩ; R_0402_1005Metric; LCSC Part Number C25879
SW1, SW2: SW_Rotary_1x5_MP; SW_Rotary_RS25-5P; Manufacturer_Part_Number RS25-16.5KQA1-1-5P(P7)-WY-WZ-V38
pot1, pot2, pot3, pot4, pot5, pot6, pot7: b10k; Potentiometer_Alps_RK09K_Single_Vertical
toggle_sw1, toggle_sw2, toggle_sw3, toggle_sw4, toggle_sw5, toggle_sw6, toggle_sw7, toggle_sw8: SW_SPST; Toggle_Switch-2-pins

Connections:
3.3V: C1.2, MUX1.24 (VCC), R7.1, R12.1, SW1.5, SW2.5, pot1.3, pot2.3, pot3.3, pot4.3, pot5.3, pot6.3, pot7.3; also elsewhere on the board
GND: C1.1, C2.1, C3.1, MUX1.12 (GND), MUX1.15 (~E), R4.2, R9.2, SW1.1, SW2.1, pot1.1, pot2.1, pot3.1, pot4.1, pot5.1, pot6.1, pot7.1, toggle_sw1.2 (B), toggle_sw2.2 (B), toggle_sw3.2 (B), toggle_sw4.2 (B), toggle_sw5.2 (B), toggle_sw6.2 (B), toggle_sw7.2 (B), toggle_sw8.2 (B); also elsewhere on the board
I0: MUX1.9 (I0), pot1.2
I1: MUX1.8 (I1), pot2.2
I2: MUX1.7 (I2), pot3.2
I3: MUX1.6 (I3), pot4.2
I4: MUX1.5 (I4), pot5.2
I5: MUX1.4 (I5), pot6.2
I6: MUX1.3 (I6), pot7.2
I7: MUX1.2 (I7), toggle_sw1.1 (A)
I8: MUX1.23 (I8), toggle_sw2.1 (A)
I9: MUX1.22 (I9), toggle_sw3.1 (A)
I10: MUX1.21 (I10), toggle_sw4.1 (A)
I11: MUX1.20 (I11), toggle_sw5.1 (A)
I12: MUX1.19 (I12), toggle_sw6.1 (A)
I13: MUX1.18 (I13), toggle_sw7.1 (A)
I14: MUX1.17 (I14), toggle_sw8.1 (A)
I15: MUX1.16 (I15), R3.1
unnamed: C2.2, R3.2, SW1.C
unnamed: C3.2, R8.2, SW2.C
unnamed: R4.1, R5.2, SW1.2
unnamed: R5.1, R6.2, SW1.3
unnamed: R6.1, R7.2, SW1.4
unnamed: R10.1, R11.2, SW2.3
unnamed: R9.1, R10.2, SW2.2
unnamed: R11.1, R12.2, SW2.4
S0: MUX1.10 (S0); also elsewhere on the board
S1: MUX1.11 (S1); also elsewhere on the board
S2: MUX1.14 (S2); also elsewhere on the board
S3: MUX1.13 (S3); also elsewhere on the board
rotary_sw_2: R8.1; also elsewhere on the board
sig_1: MUX1.1 (COM); also elsewhere on the board

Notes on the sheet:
4067
Toggle switches
Potentiometers
Rotary Switches
